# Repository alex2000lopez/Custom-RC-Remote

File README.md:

# Full Custom RC Remote
Full Custom RC Remote PCB and schematic designed for MakersUPV

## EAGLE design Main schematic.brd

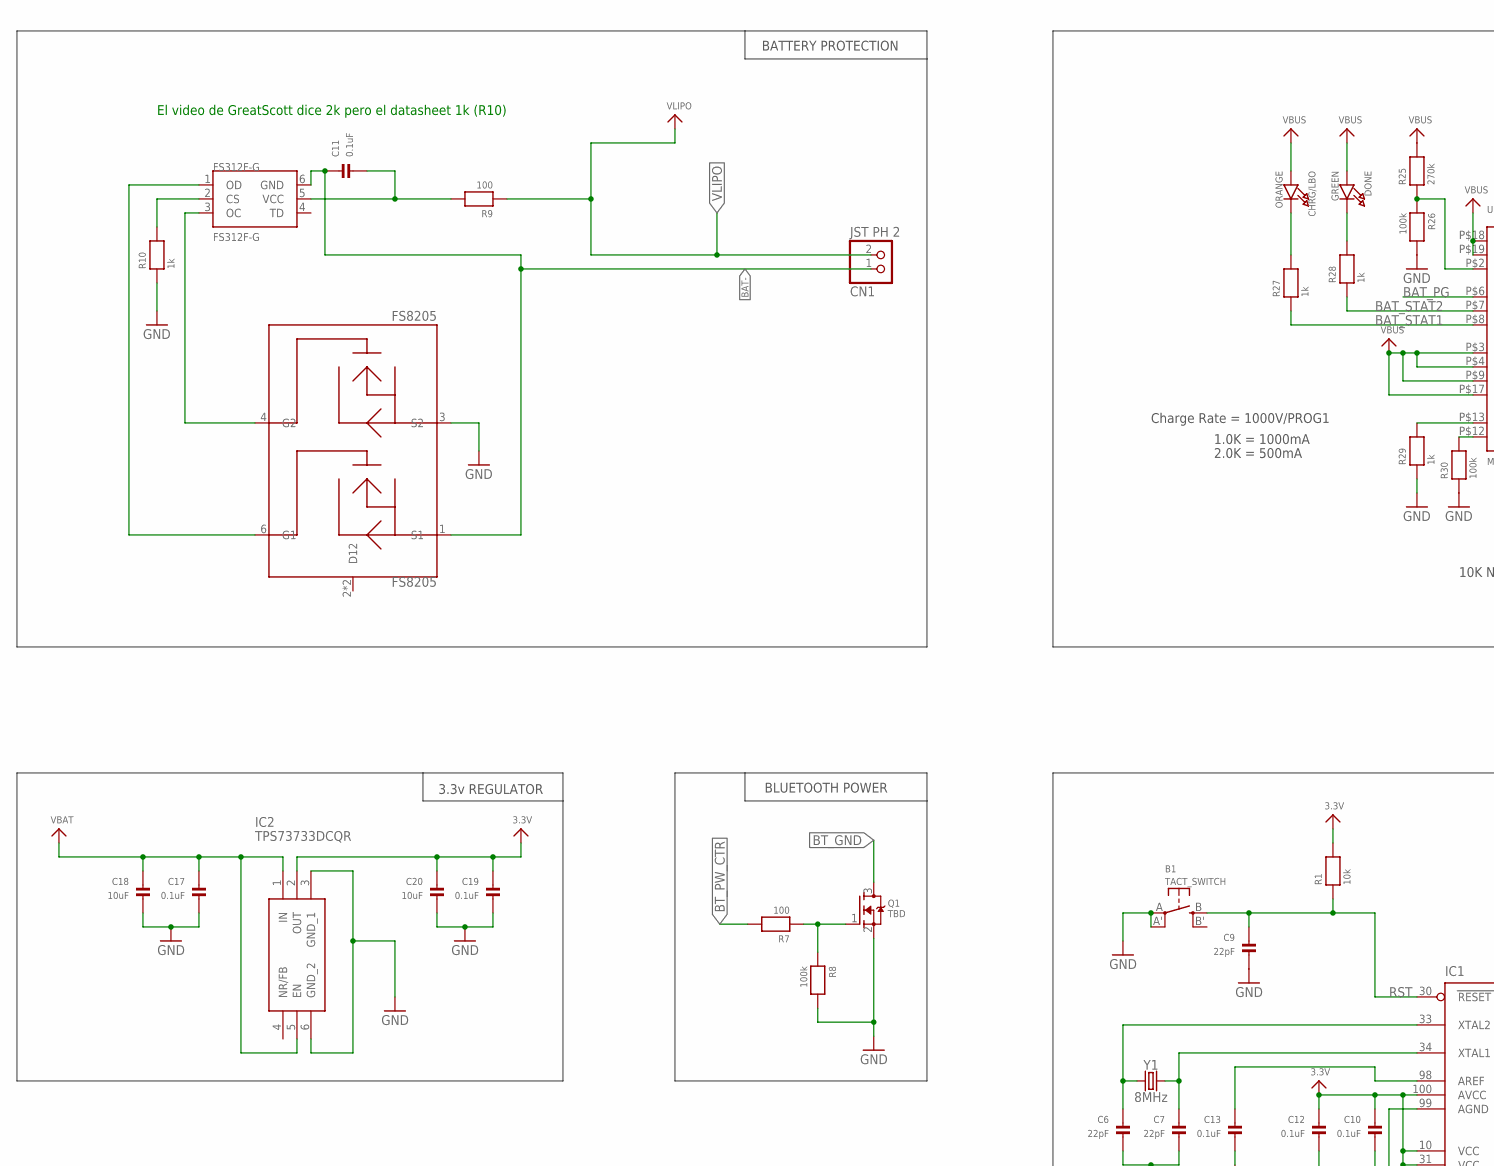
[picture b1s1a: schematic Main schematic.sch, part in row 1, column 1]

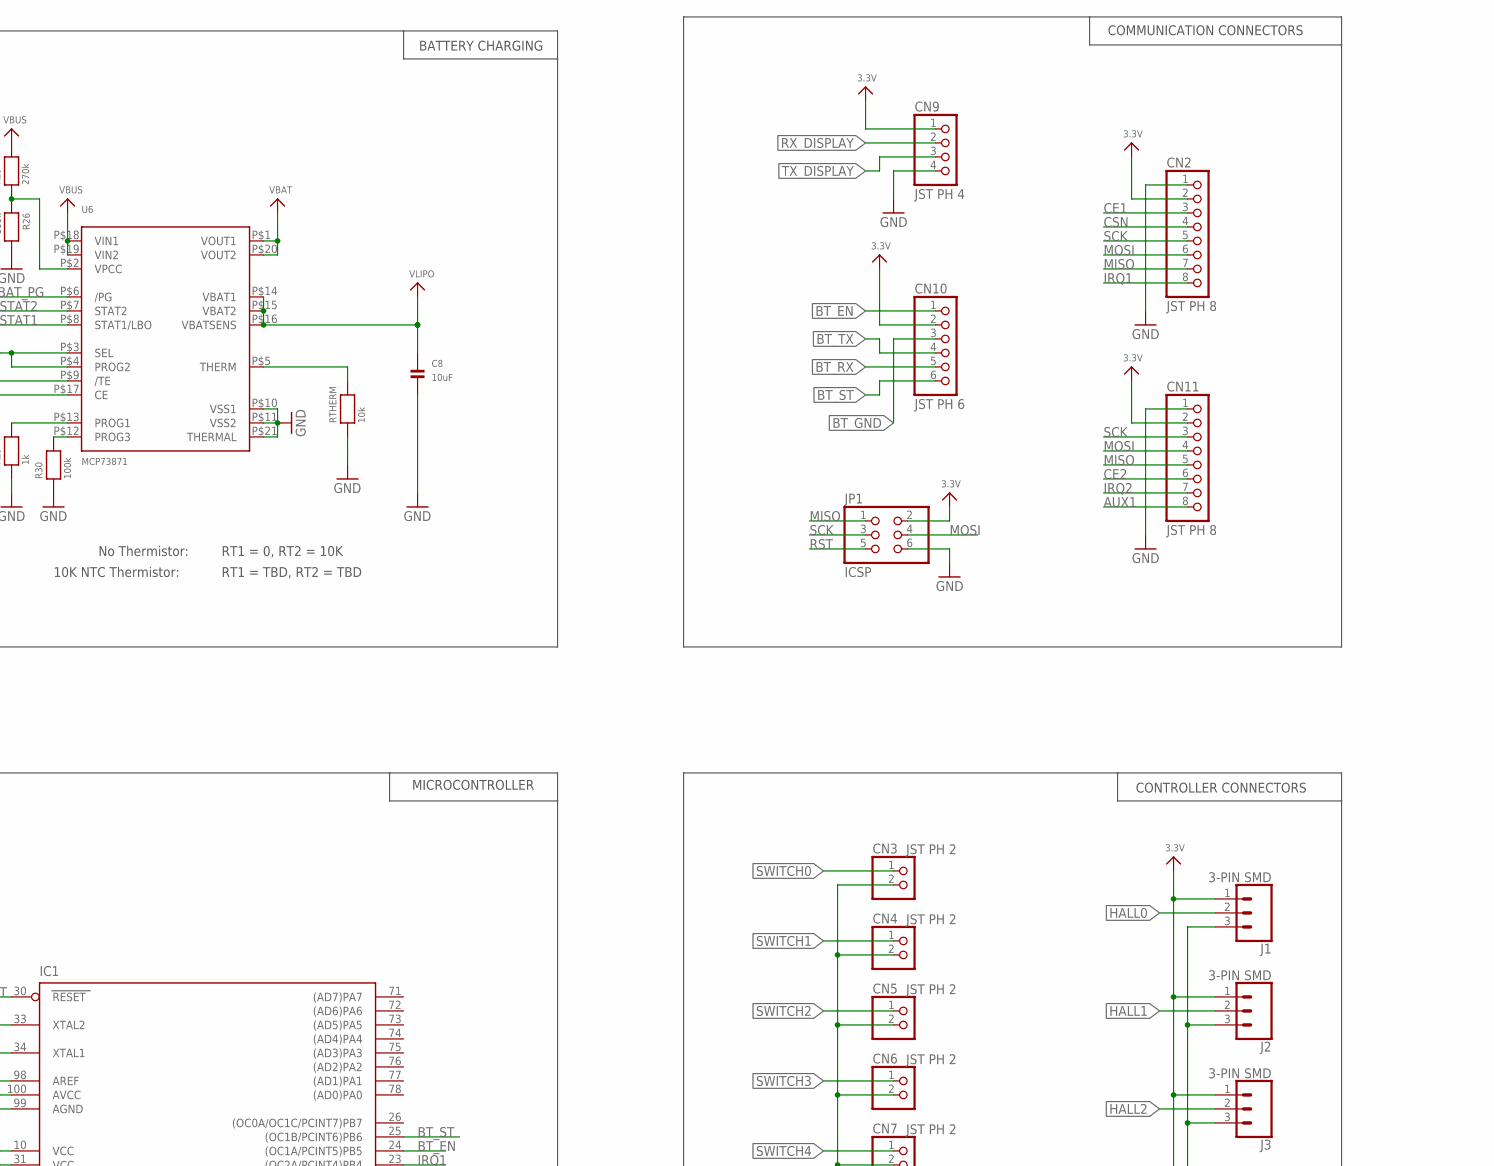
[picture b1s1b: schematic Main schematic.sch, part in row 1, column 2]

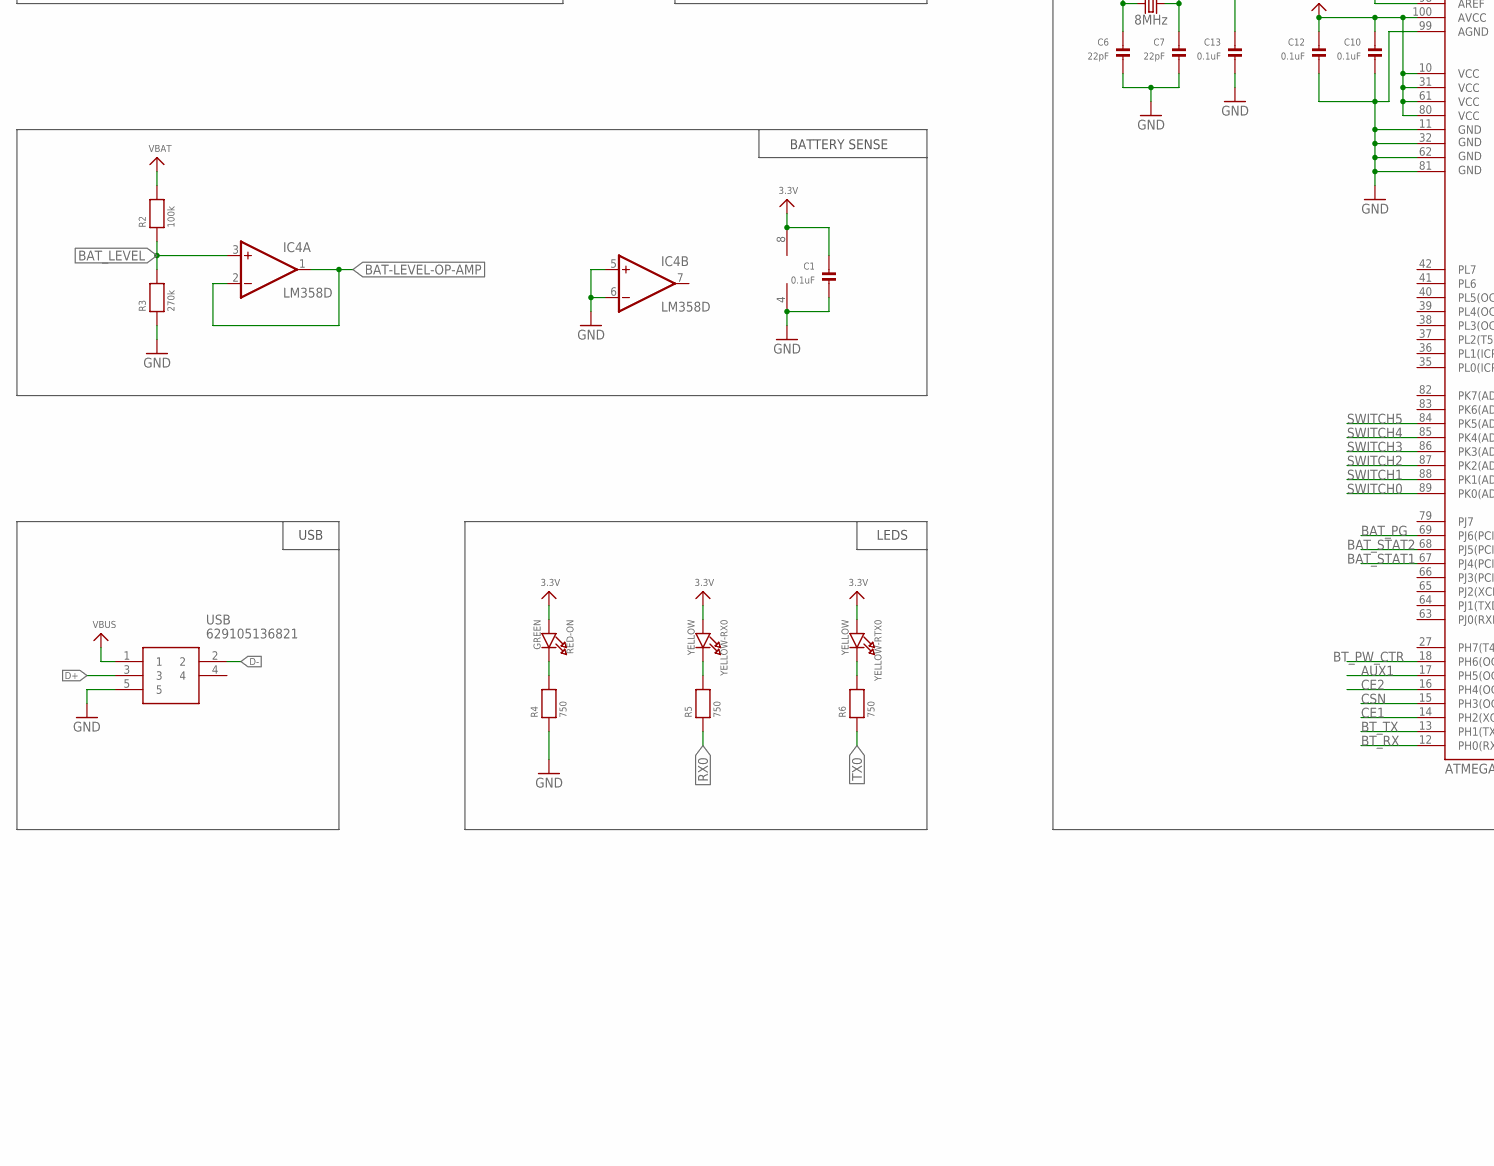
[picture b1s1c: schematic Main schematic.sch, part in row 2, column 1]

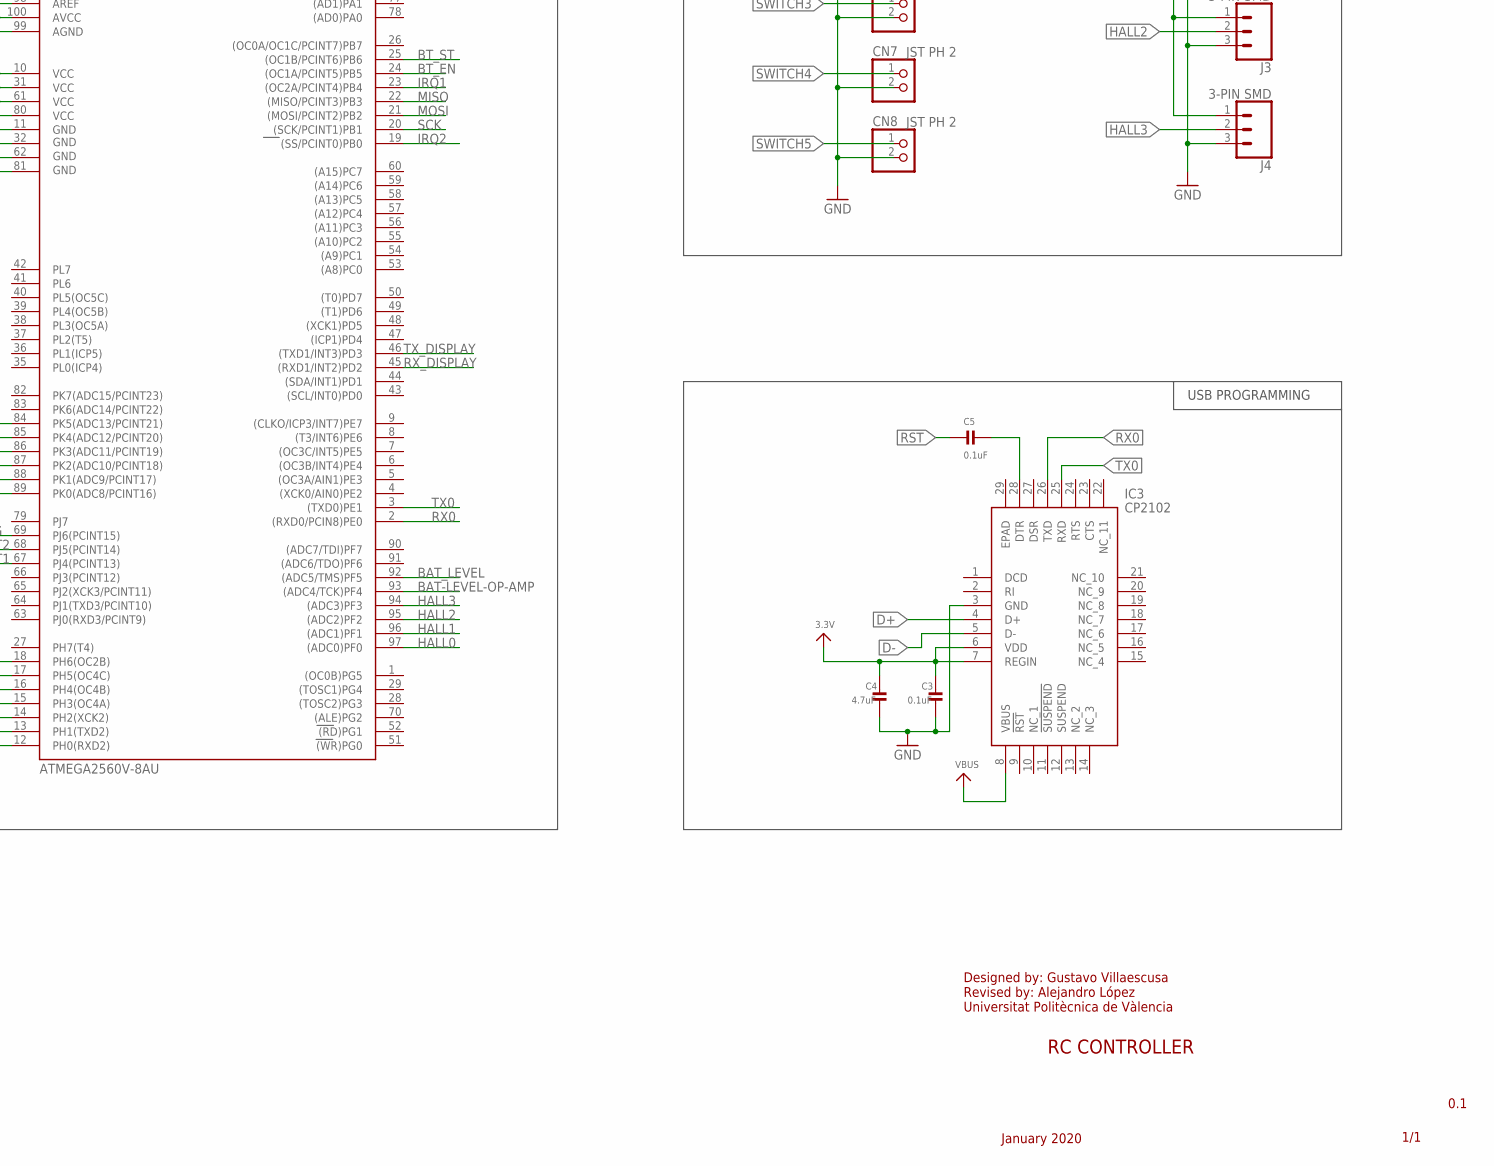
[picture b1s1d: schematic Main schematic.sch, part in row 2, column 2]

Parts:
B1: TACT_SWITCH; BTN_KMR2_4.6X2.8
C1, C3, C5, C10, C11, C12, C13, C17, C19: 0.1uF; 0805
C4: 4.7uF; 0805
C6, C7, C9: 22pF; 0805
C8, C18, C20: 10uF; 0805
CHRG/LBO: ORANGE; CHIPLED_0805
CN1, CN3, CN4, CN5, CN6, CN7, CN8: JST PH 2; JSTPH2
CN2, CN11: JST PH 8; JSTPH8
CN9: JST PH 4; JSTPH4
CN10: JST PH 6; JSTPH6
DONE: GREEN; CHIPLED_0805
FS312F-G: FS312F-G; SOT23-6
FS8205: FS8205; SOT23-6
IC1: ATMEGA2560V-8AU; TQFP100
IC2: TPS73733DCQR; SOT127P706X180-6N
IC3: CP2102; QFN50P500X500X100-29N
IC4: LM358D; SO08
J1, J2, J3, J4: 3-PIN SMD; JST-3-SMD
JP1: ICSP; 2X03_ROUND_70MIL
Q1: TBD; SOT23-WIDE
R1: 10k; 0805
R2, R8, R26, R30: 100k; 0805
R3, R25: 270k; 0805
R4, R5, R6: 750; 0805
R7, R9: 100; 0805
R10, R27, R28, R29: 1k; 0805
RED-ON: GREEN; CHIPLED_0805
RTHERM: 10k; 0805
U6: MCP73871; QFN20_4MM
USB: 629105136821; MICRO-USB(2.0-SMT-TYPE-B)
Y1: 8MHz; HC49UP
YELLOW-RTX0: YELLOW; CHIPLED_0805
YELLOW-RX0: YELLOW; CHIPLED_0805

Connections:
3.3V: C1.1, C3.1, C4.1, C10.1, C12.1, C19.1, C20.1, CN2.2, CN9.1, CN10.2, CN11.2, IC1.10 (VCC), IC1.31 (VCC1), IC1.61 (VCC2), IC1.80 (VCC3), IC1.100 (AVCC), IC2.2 (OUT), IC3.6 (VDD), IC3.7 (REGIN), IC4.8 (V+), J1.1, J2.1, J3.1, J4.1, JP1.2, R1.2, RED-ON.A, YELLOW-RTX0.A, YELLOW-RX0.A
AUX1: CN11.8, IC1.17 (PH5(OC4C))
BAT-: C11.1, CN1.1, FS312F-G.6 (GND), FS8205.1 (S1)
BAT-LEVEL-OP-AMP: IC1.93 ((ADC4/TCK)PF4), IC4.1 (OUT), IC4.2 (-IN)
BAT_LEVEL: IC1.92 ((ADC5/TMS)PF5), IC4.3 (+IN), R2.1, R3.2
BAT_PG: IC1.69 (PJ6(PCINT15)), U6.P$6 (/PG)
BAT_STAT1: IC1.67 (PJ4(PCINT13)), R27.1, U6.P$8 (STAT1/LBO)
BAT_STAT2: IC1.68 (PJ5(PCINT14)), R28.1, U6.P$7 (STAT2)
BT_EN: CN10.1, IC1.24 ((OC1A/PCINT5)PB5)
BT_GND: CN10.3, Q1.3 (D)
BT_PW_CTR: IC1.18 (PH6(OC2B)), R7.2
BT_RX: CN10.5, IC1.12 (PH0(RXD2))
BT_ST: CN10.6, IC1.25 ((OC1B/PCINT6)PB6)
BT_TX: CN10.4, IC1.13 (PH1(TXD2))
CE1: CN2.3, IC1.14 (PH2(XCK2))
CE2: CN11.6, IC1.16 (PH4(OC4B))
CSN: CN2.4, IC1.15 (PH3(OC4A))
D+: IC3.4 (D+), USB.3
D-: IC3.5 (D-), USB.2
GND: B1.A, B1.A' (P1), C1.2, C3.2, C4.2, C6.2, C7.2, C8.2, C9.2, C10.2, C12.2, C13.2, C17.2, C18.2, C19.2, C20.2, CN2.1, CN3.2, CN4.2, CN5.2, CN6.2, CN7.2, CN8.2, CN9.4, CN11.1, FS8205.3 (S2), IC1.11 (GND), IC1.32 (GND1), IC1.62 (GND2), IC1.81 (GND3), IC1.99 (AGND), IC2.3 (GND_1), IC2.6 (GND_2), IC3.3 (GND), IC4.4 (V-), IC4.5 (+IN), IC4.6 (-IN), J1.3, J2.3, J3.3, J4.3, JP1.6, Q1.2 (S), R3.1, R4.1, R8.2, R10.1, R26.2, R29.1, R30.1, RTHERM.1, U6.P$10 (VSS1), U6.P$11 (VSS2), U6.P$21 (THERMAL), USB.5
GREEN: DONE.C, R28.2
HALL0: IC1.97 ((ADC0)PF0), J1.2
HALL1: IC1.96 ((ADC1)PF1), J2.2
HALL2: IC1.95 ((ADC2)PF2), J3.2
HALL3: IC1.94 ((ADC3)PF3), J4.2
IRQ1: CN2.8, IC1.23 ((OC2A/PCINT4)PB4)
IRQ2: CN11.7, IC1.19 ((SS/PCINT0)PB0)
MISO: CN2.7, CN11.5, IC1.22 ((MISO/PCINT3)PB3), JP1.1
MOSI: CN2.6, CN11.4, IC1.21 ((MOSI/PCINT2)PB2), JP1.4
unnamed: C6.1, IC1.33 (XTAL2), Y1.1
unnamed: C13.1, IC1.98 (AREF)
unnamed: C5.1, IC3.28 (DTR)
unnamed: C7.1, IC1.34 (XTAL1), Y1.2
unnamed: R4.2, RED-ON.C
unnamed: R5.2, YELLOW-RX0.C
unnamed: RTHERM.2, U6.P$5 (THERM)
unnamed: R25.1, R26.1, U6.P$2 (VPCC)
unnamed: R6.2, YELLOW-RTX0.C
unnamed: C11.2, FS312F-G.5 (VCC), R9.2
unnamed: Q1.1 (G), R7.1, R8.1
unnamed: FS312F-G.3 (OC), FS8205.4 (G2)
unnamed: FS312F-G.1 (OD), FS8205.6 (G1)
unnamed: FS312F-G.2 (CS), R10.2
unnamed: R29.2, U6.P$13 (PROG1)
unnamed: R30.2, U6.P$12 (PROG3)
ORANGE: CHRG/LBO.C, R27.2
RST: B1.B (S), C5.2, C9.1, IC1.30 (RESET), JP1.5, R1.1
RX0: IC1.2 ((RXD0/PCIN8)PE0), IC3.26 (TXD), R5.1
RX_DISPLAY: CN9.2, IC1.45 ((RXD1/INT2)PD2)
SCK: CN2.5, CN11.3, IC1.20 ((SCK/PCINT1)PB1), JP1.3
SWITCH0: CN3.1, IC1.89 (PK0(ADC8/PCINT16))
SWITCH1: CN4.1, IC1.88 (PK1(ADC9/PCINT17))
SWITCH2: CN5.1, IC1.87 (PK2(ADC10/PCINT18))
SWITCH3: CN6.1, IC1.86 (PK3(ADC11/PCINT19))
SWITCH4: CN7.1, IC1.85 (PK4(ADC12/PCINT20))
SWITCH5: CN8.1, IC1.84 (PK5(ADC13/PCINT21))
TX0: IC1.3 ((TXD0)PE1), IC3.25 (RXD), R6.1
TX_DISPLAY: CN9.3, IC1.46 ((TXD1/INT3)PD3)
VBAT: C17.1, C18.1, IC2.1 (IN), IC2.5 (EN), R2.2, U6.P$1 (VOUT1), U6.P$20 (VOUT2)
VBUS: CHRG/LBO.A, DONE.A, IC3.8 (VBUS), R25.2, U6.P$3 (SEL), U6.P$4 (PROG2), U6.P$9 (/TE), U6.P$17 (CE), U6.P$18 (VIN1), U6.P$19 (VIN2), USB.1
VLIPO: C8.1, CN1.2, R9.1, U6.P$14 (VBAT1), U6.P$15 (VBAT2), U6.P$16 (VBATSENS)

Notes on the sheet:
Charge Rate = 1000V/PROG1
1.0K = 1000mA
2.0K = 500mA
No Thermistor:
10K NTC Thermistor:
RT1 = 0, RT2 = 10K
RT1 = TBD, RT2 = TBD
BATTERY CHARGING
El video de GreatScott dice 2k pero el datasheet 1k (R10)
BATTERY PROTECTION
3.3v REGULATOR
COMMUNICATION CONNECTORS
CONTROLLER CONNECTORS
BATTERY SENSE
USB
LEDS
BLUETOOTH POWER
USB PROGRAMMING
MICROCONTROLLER
RC CONTROLLER
0.1
Designed by: Gustavo Villaescusa Revised by: Alejandro López Universitat Politècnica de Vàlencia
January 2020
1/1

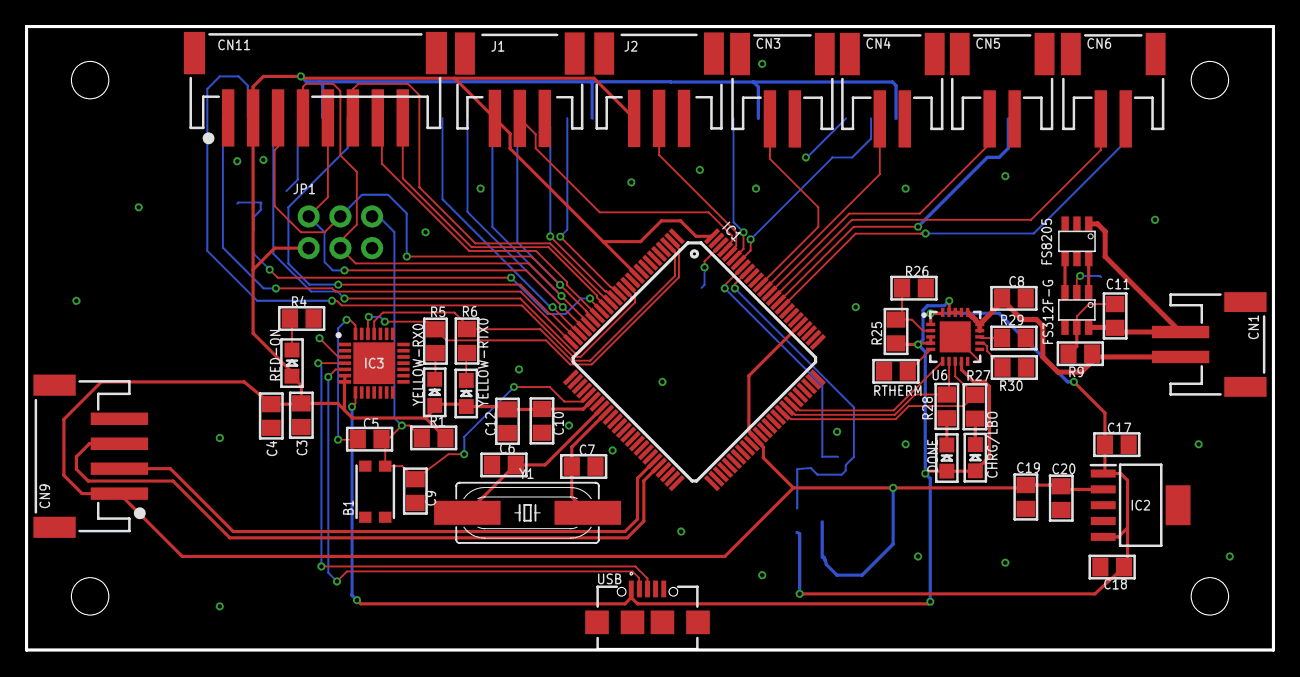
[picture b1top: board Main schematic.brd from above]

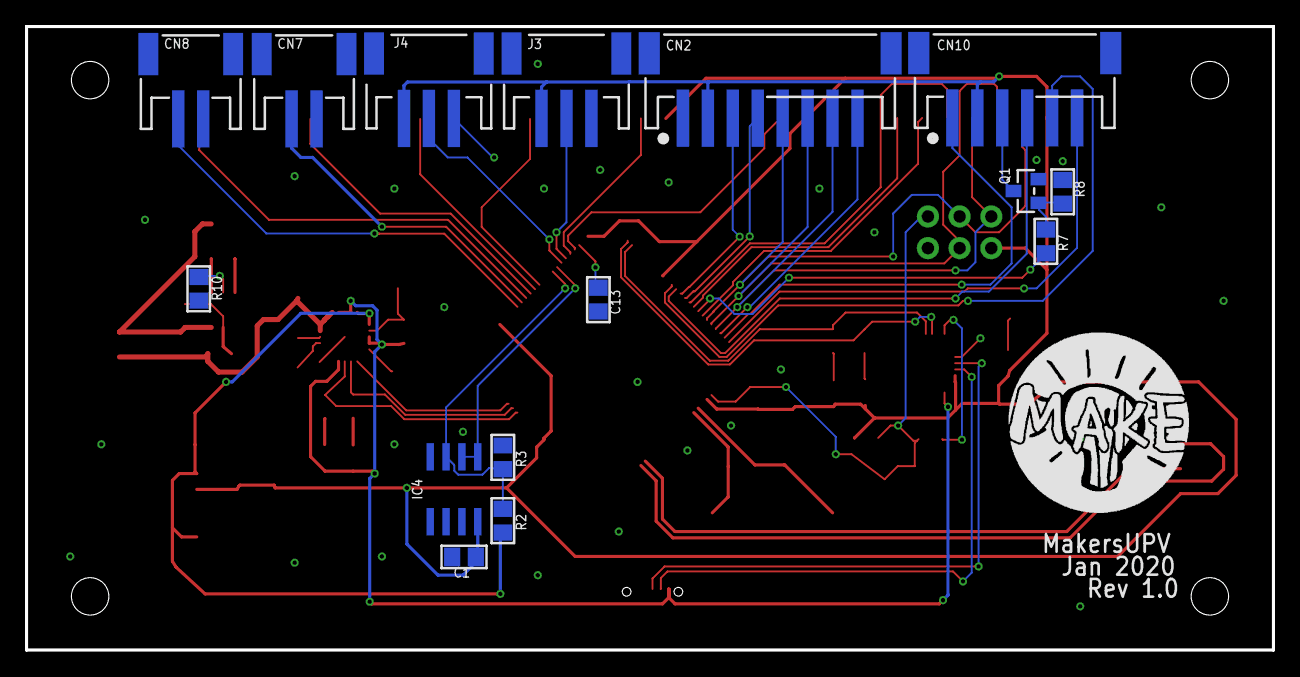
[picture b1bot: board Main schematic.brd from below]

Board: 2 copper layers, 100.0 x 50.0 mm, 65 parts (15 on the bottom side), 61 nets.

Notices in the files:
parts and their libraries:
microbuilder: This work is placed in the public domain, and may be freely used for commercial and non-commercial work with the following conditions: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
SparkFun-Connectors: Licensing: Creative Commons ShareAlike 4.0 International - https://creativecommons.org/licenses/by-sa/4.0
